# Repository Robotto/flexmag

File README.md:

[Interactive BOM here](https://htmlpreview.github.io/?https://github.com/robotto/flexmag/blob/master/bom/ibom.html)

[View schematic and board with KiCanvas here](https://kicanvas.org/?github=https%3A%2F%2Fgithub.com%2FRobotto%2Fflexmag)

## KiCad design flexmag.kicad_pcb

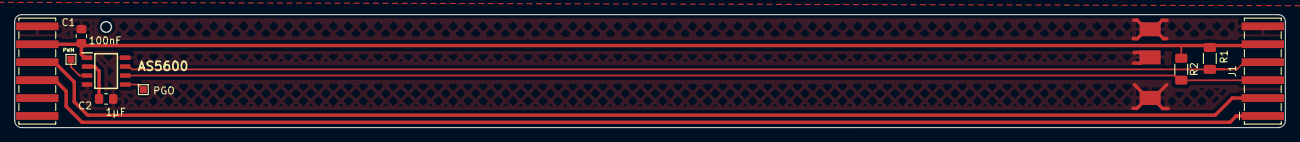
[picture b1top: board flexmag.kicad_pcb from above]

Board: 2 copper layers, 179.9 x 16.0 mm, 7 parts (0 on the bottom side), 7 nets.

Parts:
AS5600: AS5600-ASOM; SOIC127P600X175-8N
C1: 100nF; R_0805_2012Metric_Pad1.20x1.40mm_HandSolder
C2: 1µF; R_0805_2012Metric_Pad1.20x1.40mm_HandSolder
J1, J2: Conn_01x06_Male; FLATCON
R1, R2: 10K; R_1206_3216Metric_Pad1.30x1.75mm_HandSolder

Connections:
+5V: AS5600.1 (VDD5V), C1.1, J1.5, J2.5, R1.1, R2.1
GND: AS5600.4 (GND), AS5600.8 (DIR), C1.2, C2.2, J1.6, J2.6
unnamed: AS5600.2 (VDD3V3), C2.1
unnamed: J1.1, J2.3
unnamed: J1.2, J2.4
unnamed: AS5600.6 (SDA), J1.3, R2.2
unnamed: AS5600.7 (SCL), J1.4, R1.2

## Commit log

2023-10-23 Init
2023-10-23 interactive bom
2023-10-23 readme
2023-10-23 readme stuff
2023-10-23 now as sigle sided PCB
2023-10-26 Perfect is the enemy of done
2023-12-16 changes??
